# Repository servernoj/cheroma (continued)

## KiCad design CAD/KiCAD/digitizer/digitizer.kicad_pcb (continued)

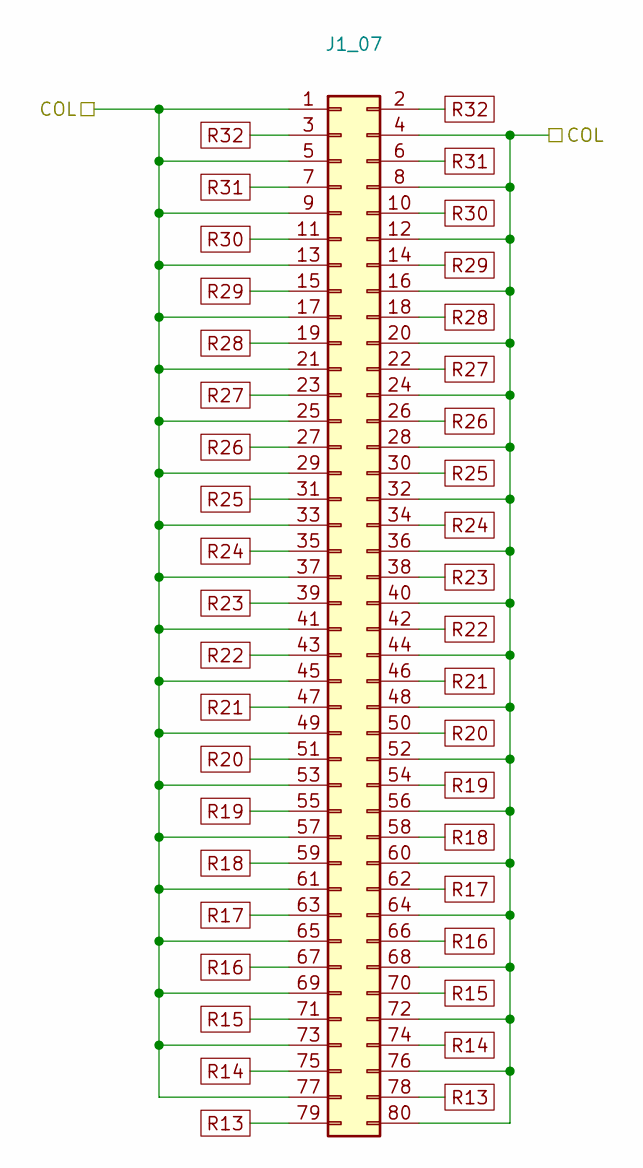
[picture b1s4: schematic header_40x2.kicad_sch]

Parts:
J1_07: Conn_02x40_Odd_Even; PinHeader_2x40_P2.54mm_Vertical

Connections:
C7: J1_07.1, J1_07.4, J1_07.5, J1_07.8, J1_07.9, J1_07.12, J1_07.13, J1_07.16, J1_07.17, J1_07.20, J1_07.21, J1_07.24, J1_07.25, J1_07.28, J1_07.29, J1_07.32, J1_07.33, J1_07.36, J1_07.37, J1_07.40, J1_07.41, J1_07.44, J1_07.45, J1_07.48, J1_07.49, J1_07.52, J1_07.53, J1_07.56, J1_07.57, J1_07.60, J1_07.61, J1_07.64, J1_07.65, J1_07.68, J1_07.69, J1_07.72, J1_07.73, J1_07.76, J1_07.77, J1_07.80; also elsewhere on the board
R13: J1_07.78, J1_07.79; also elsewhere on the board
R14: J1_07.74, J1_07.75; also elsewhere on the board
R15: J1_07.70, J1_07.71; also elsewhere on the board
R16: J1_07.66, J1_07.67; also elsewhere on the board
R17: J1_07.62, J1_07.63; also elsewhere on the board
R18: J1_07.58, J1_07.59; also elsewhere on the board
R19: J1_07.54, J1_07.55; also elsewhere on the board
R20: J1_07.50, J1_07.51; also elsewhere on the board
R21: J1_07.46, J1_07.47; also elsewhere on the board
R22: J1_07.42, J1_07.43; also elsewhere on the board
R23: J1_07.38, J1_07.39; also elsewhere on the board
R24: J1_07.34, J1_07.35; also elsewhere on the board
R25: J1_07.30, J1_07.31; also elsewhere on the board
R26: J1_07.26, J1_07.27; also elsewhere on the board
R27: J1_07.22, J1_07.23; also elsewhere on the board
R28: J1_07.18, J1_07.19; also elsewhere on the board
R29: J1_07.14, J1_07.15; also elsewhere on the board
R30: J1_07.10, J1_07.11; also elsewhere on the board
R31: J1_07.6, J1_07.7; also elsewhere on the board
R32: J1_07.2, J1_07.3; also elsewhere on the board

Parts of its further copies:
J1_01, J1_02, J1_03, J1_04, J1_05, J1_06, J1_08, J1_09, J1_10, J1_11, J1_12, J1_13, J1_14, J1_15, J1_16, J1_17, J1_18, J1_19, J1_20, J1_21, J1_22, J1_23, J1_24, J1_25, J1_26, J1_27, J1_28, J1_29, J1_30, J1_31, J1_32: Conn_02x40_Odd_Even; PinHeader_2x40_P2.54mm_Vertical

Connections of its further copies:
C1: J1_01.1, J1_01.4, J1_01.5, J1_01.8, J1_01.9, J1_01.12, J1_01.13, J1_01.16, J1_01.17, J1_01.20, J1_01.21, J1_01.24, J1_01.25, J1_01.28, J1_01.29, J1_01.32, J1_01.33, J1_01.36, J1_01.37, J1_01.40, J1_01.41, J1_01.44, J1_01.45, J1_01.48, J1_01.49, J1_01.52, J1_01.53, J1_01.56, J1_01.57, J1_01.60, J1_01.61, J1_01.64, J1_01.65, J1_01.68, J1_01.69, J1_01.72, J1_01.73, J1_01.76, J1_01.77, J1_01.80; also elsewhere on the board
C2: J1_02.1, J1_02.4, J1_02.5, J1_02.8, J1_02.9, J1_02.12, J1_02.13, J1_02.16, J1_02.17, J1_02.20, J1_02.21, J1_02.24, J1_02.25, J1_02.28, J1_02.29, J1_02.32, J1_02.33, J1_02.36, J1_02.37, J1_02.40, J1_02.41, J1_02.44, J1_02.45, J1_02.48, J1_02.49, J1_02.52, J1_02.53, J1_02.56, J1_02.57, J1_02.60, J1_02.61, J1_02.64, J1_02.65, J1_02.68, J1_02.69, J1_02.72, J1_02.73, J1_02.76, J1_02.77, J1_02.80; also elsewhere on the board
C3: J1_03.1, J1_03.4, J1_03.5, J1_03.8, J1_03.9, J1_03.12, J1_03.13, J1_03.16, J1_03.17, J1_03.20, J1_03.21, J1_03.24, J1_03.25, J1_03.28, J1_03.29, J1_03.32, J1_03.33, J1_03.36, J1_03.37, J1_03.40, J1_03.41, J1_03.44, J1_03.45, J1_03.48, J1_03.49, J1_03.52, J1_03.53, J1_03.56, J1_03.57, J1_03.60, J1_03.61, J1_03.64, J1_03.65, J1_03.68, J1_03.69, J1_03.72, J1_03.73, J1_03.76, J1_03.77, J1_03.80; also elsewhere on the board
C4: J1_04.1, J1_04.4, J1_04.5, J1_04.8, J1_04.9, J1_04.12, J1_04.13, J1_04.16, J1_04.17, J1_04.20, J1_04.21, J1_04.24, J1_04.25, J1_04.28, J1_04.29, J1_04.32, J1_04.33, J1_04.36, J1_04.37, J1_04.40, J1_04.41, J1_04.44, J1_04.45, J1_04.48, J1_04.49, J1_04.52, J1_04.53, J1_04.56, J1_04.57, J1_04.60, J1_04.61, J1_04.64, J1_04.65, J1_04.68, J1_04.69, J1_04.72, J1_04.73, J1_04.76, J1_04.77, J1_04.80; also elsewhere on the board
C5: J1_05.1, J1_05.4, J1_05.5, J1_05.8, J1_05.9, J1_05.12, J1_05.13, J1_05.16, J1_05.17, J1_05.20, J1_05.21, J1_05.24, J1_05.25, J1_05.28, J1_05.29, J1_05.32, J1_05.33, J1_05.36, J1_05.37, J1_05.40, J1_05.41, J1_05.44, J1_05.45, J1_05.48, J1_05.49, J1_05.52, J1_05.53, J1_05.56, J1_05.57, J1_05.60, J1_05.61, J1_05.64, J1_05.65, J1_05.68, J1_05.69, J1_05.72, J1_05.73, J1_05.76, J1_05.77, J1_05.80; also elsewhere on the board
C6: J1_06.1, J1_06.4, J1_06.5, J1_06.8, J1_06.9, J1_06.12, J1_06.13, J1_06.16, J1_06.17, J1_06.20, J1_06.21, J1_06.24, J1_06.25, J1_06.28, J1_06.29, J1_06.32, J1_06.33, J1_06.36, J1_06.37, J1_06.40, J1_06.41, J1_06.44, J1_06.45, J1_06.48, J1_06.49, J1_06.52, J1_06.53, J1_06.56, J1_06.57, J1_06.60, J1_06.61, J1_06.64, J1_06.65, J1_06.68, J1_06.69, J1_06.72, J1_06.73, J1_06.76, J1_06.77, J1_06.80; also elsewhere on the board
C8: J1_08.1, J1_08.4, J1_08.5, J1_08.8, J1_08.9, J1_08.12, J1_08.13, J1_08.16, J1_08.17, J1_08.20, J1_08.21, J1_08.24, J1_08.25, J1_08.28, J1_08.29, J1_08.32, J1_08.33, J1_08.36, J1_08.37, J1_08.40, J1_08.41, J1_08.44, J1_08.45, J1_08.48, J1_08.49, J1_08.52, J1_08.53, J1_08.56, J1_08.57, J1_08.60, J1_08.61, J1_08.64, J1_08.65, J1_08.68, J1_08.69, J1_08.72, J1_08.73, J1_08.76, J1_08.77, J1_08.80; also elsewhere on the board
C9: J1_09.1, J1_09.4, J1_09.5, J1_09.8, J1_09.9, J1_09.12, J1_09.13, J1_09.16, J1_09.17, J1_09.20, J1_09.21, J1_09.24, J1_09.25, J1_09.28, J1_09.29, J1_09.32, J1_09.33, J1_09.36, J1_09.37, J1_09.40, J1_09.41, J1_09.44, J1_09.45, J1_09.48, J1_09.49, J1_09.52, J1_09.53, J1_09.56, J1_09.57, J1_09.60, J1_09.61, J1_09.64, J1_09.65, J1_09.68, J1_09.69, J1_09.72, J1_09.73, J1_09.76, J1_09.77, J1_09.80; also elsewhere on the board
C10: J1_10.1, J1_10.4, J1_10.5, J1_10.8, J1_10.9, J1_10.12, J1_10.13, J1_10.16, J1_10.17, J1_10.20, J1_10.21, J1_10.24, J1_10.25, J1_10.28, J1_10.29, J1_10.32, J1_10.33, J1_10.36, J1_10.37, J1_10.40, J1_10.41, J1_10.44, J1_10.45, J1_10.48, J1_10.49, J1_10.52, J1_10.53, J1_10.56, J1_10.57, J1_10.60, J1_10.61, J1_10.64, J1_10.65, J1_10.68, J1_10.69, J1_10.72, J1_10.73, J1_10.76, J1_10.77, J1_10.80; also elsewhere on the board
C11: J1_11.1, J1_11.4, J1_11.5, J1_11.8, J1_11.9, J1_11.12, J1_11.13, J1_11.16, J1_11.17, J1_11.20, J1_11.21, J1_11.24, J1_11.25, J1_11.28, J1_11.29, J1_11.32, J1_11.33, J1_11.36, J1_11.37, J1_11.40, J1_11.41, J1_11.44, J1_11.45, J1_11.48, J1_11.49, J1_11.52, J1_11.53, J1_11.56, J1_11.57, J1_11.60, J1_11.61, J1_11.64, J1_11.65, J1_11.68, J1_11.69, J1_11.72, J1_11.73, J1_11.76, J1_11.77, J1_11.80; also elsewhere on the board
C12: J1_12.1, J1_12.4, J1_12.5, J1_12.8, J1_12.9, J1_12.12, J1_12.13, J1_12.16, J1_12.17, J1_12.20, J1_12.21, J1_12.24, J1_12.25, J1_12.28, J1_12.29, J1_12.32, J1_12.33, J1_12.36, J1_12.37, J1_12.40, J1_12.41, J1_12.44, J1_12.45, J1_12.48, J1_12.49, J1_12.52, J1_12.53, J1_12.56, J1_12.57, J1_12.60, J1_12.61, J1_12.64, J1_12.65, J1_12.68, J1_12.69, J1_12.72, J1_12.73, J1_12.76, J1_12.77, J1_12.80; also elsewhere on the board
C13: J1_13.1, J1_13.4, J1_13.5, J1_13.8, J1_13.9, J1_13.12, J1_13.13, J1_13.16, J1_13.17, J1_13.20, J1_13.21, J1_13.24, J1_13.25, J1_13.28, J1_13.29, J1_13.32, J1_13.33, J1_13.36, J1_13.37, J1_13.40, J1_13.41, J1_13.44, J1_13.45, J1_13.48, J1_13.49, J1_13.52, J1_13.53, J1_13.56, J1_13.57, J1_13.60, J1_13.61, J1_13.64, J1_13.65, J1_13.68, J1_13.69, J1_13.72, J1_13.73, J1_13.76, J1_13.77, J1_13.80; also elsewhere on the board
C14: J1_14.1, J1_14.4, J1_14.5, J1_14.8, J1_14.9, J1_14.12, J1_14.13, J1_14.16, J1_14.17, J1_14.20, J1_14.21, J1_14.24, J1_14.25, J1_14.28, J1_14.29, J1_14.32, J1_14.33, J1_14.36, J1_14.37, J1_14.40, J1_14.41, J1_14.44, J1_14.45, J1_14.48, J1_14.49, J1_14.52, J1_14.53, J1_14.56, J1_14.57, J1_14.60, J1_14.61, J1_14.64, J1_14.65, J1_14.68, J1_14.69, J1_14.72, J1_14.73, J1_14.76, J1_14.77, J1_14.80; also elsewhere on the board
C15: J1_15.1, J1_15.4, J1_15.5, J1_15.8, J1_15.9, J1_15.12, J1_15.13, J1_15.16, J1_15.17, J1_15.20, J1_15.21, J1_15.24, J1_15.25, J1_15.28, J1_15.29, J1_15.32, J1_15.33, J1_15.36, J1_15.37, J1_15.40, J1_15.41, J1_15.44, J1_15.45, J1_15.48, J1_15.49, J1_15.52, J1_15.53, J1_15.56, J1_15.57, J1_15.60, J1_15.61, J1_15.64, J1_15.65, J1_15.68, J1_15.69, J1_15.72, J1_15.73, J1_15.76, J1_15.77, J1_15.80; also elsewhere on the board
C16: J1_16.1, J1_16.4, J1_16.5, J1_16.8, J1_16.9, J1_16.12, J1_16.13, J1_16.16, J1_16.17, J1_16.20, J1_16.21, J1_16.24, J1_16.25, J1_16.28, J1_16.29, J1_16.32, J1_16.33, J1_16.36, J1_16.37, J1_16.40, J1_16.41, J1_16.44, J1_16.45, J1_16.48, J1_16.49, J1_16.52, J1_16.53, J1_16.56, J1_16.57, J1_16.60, J1_16.61, J1_16.64, J1_16.65, J1_16.68, J1_16.69, J1_16.72, J1_16.73, J1_16.76, J1_16.77, J1_16.80; also elsewhere on the board
C17: J1_17.1, J1_17.4, J1_17.5, J1_17.8, J1_17.9, J1_17.12, J1_17.13, J1_17.16, J1_17.17, J1_17.20, J1_17.21, J1_17.24, J1_17.25, J1_17.28, J1_17.29, J1_17.32, J1_17.33, J1_17.36, J1_17.37, J1_17.40, J1_17.41, J1_17.44, J1_17.45, J1_17.48, J1_17.49, J1_17.52, J1_17.53, J1_17.56, J1_17.57, J1_17.60, J1_17.61, J1_17.64, J1_17.65, J1_17.68, J1_17.69, J1_17.72, J1_17.73, J1_17.76, J1_17.77, J1_17.80; also elsewhere on the board
C18: J1_18.1, J1_18.4, J1_18.5, J1_18.8, J1_18.9, J1_18.12, J1_18.13, J1_18.16, J1_18.17, J1_18.20, J1_18.21, J1_18.24, J1_18.25, J1_18.28, J1_18.29, J1_18.32, J1_18.33, J1_18.36, J1_18.37, J1_18.40, J1_18.41, J1_18.44, J1_18.45, J1_18.48, J1_18.49, J1_18.52, J1_18.53, J1_18.56, J1_18.57, J1_18.60, J1_18.61, J1_18.64, J1_18.65, J1_18.68, J1_18.69, J1_18.72, J1_18.73, J1_18.76, J1_18.77, J1_18.80; also elsewhere on the board
C19: J1_19.1, J1_19.4, J1_19.5, J1_19.8, J1_19.9, J1_19.12, J1_19.13, J1_19.16, J1_19.17, J1_19.20, J1_19.21, J1_19.24, J1_19.25, J1_19.28, J1_19.29, J1_19.32, J1_19.33, J1_19.36, J1_19.37, J1_19.40, J1_19.41, J1_19.44, J1_19.45, J1_19.48, J1_19.49, J1_19.52, J1_19.53, J1_19.56, J1_19.57, J1_19.60, J1_19.61, J1_19.64, J1_19.65, J1_19.68, J1_19.69, J1_19.72, J1_19.73, J1_19.76, J1_19.77, J1_19.80; also elsewhere on the board
C20: J1_20.1, J1_20.4, J1_20.5, J1_20.8, J1_20.9, J1_20.12, J1_20.13, J1_20.16, J1_20.17, J1_20.20, J1_20.21, J1_20.24, J1_20.25, J1_20.28, J1_20.29, J1_20.32, J1_20.33, J1_20.36, J1_20.37, J1_20.40, J1_20.41, J1_20.44, J1_20.45, J1_20.48, J1_20.49, J1_20.52, J1_20.53, J1_20.56, J1_20.57, J1_20.60, J1_20.61, J1_20.64, J1_20.65, J1_20.68, J1_20.69, J1_20.72, J1_20.73, J1_20.76, J1_20.77, J1_20.80; also elsewhere on the board
C21: J1_21.1, J1_21.4, J1_21.5, J1_21.8, J1_21.9, J1_21.12, J1_21.13, J1_21.16, J1_21.17, J1_21.20, J1_21.21, J1_21.24, J1_21.25, J1_21.28, J1_21.29, J1_21.32, J1_21.33, J1_21.36, J1_21.37, J1_21.40, J1_21.41, J1_21.44, J1_21.45, J1_21.48, J1_21.49, J1_21.52, J1_21.53, J1_21.56, J1_21.57, J1_21.60, J1_21.61, J1_21.64, J1_21.65, J1_21.68, J1_21.69, J1_21.72, J1_21.73, J1_21.76, J1_21.77, J1_21.80; also elsewhere on the board
C22: J1_22.1, J1_22.4, J1_22.5, J1_22.8, J1_22.9, J1_22.12, J1_22.13, J1_22.16, J1_22.17, J1_22.20, J1_22.21, J1_22.24, J1_22.25, J1_22.28, J1_22.29, J1_22.32, J1_22.33, J1_22.36, J1_22.37, J1_22.40, J1_22.41, J1_22.44, J1_22.45, J1_22.48, J1_22.49, J1_22.52, J1_22.53, J1_22.56, J1_22.57, J1_22.60, J1_22.61, J1_22.64, J1_22.65, J1_22.68, J1_22.69, J1_22.72, J1_22.73, J1_22.76, J1_22.77, J1_22.80; also elsewhere on the board
C23: J1_23.1, J1_23.4, J1_23.5, J1_23.8, J1_23.9, J1_23.12, J1_23.13, J1_23.16, J1_23.17, J1_23.20, J1_23.21, J1_23.24, J1_23.25, J1_23.28, J1_23.29, J1_23.32, J1_23.33, J1_23.36, J1_23.37, J1_23.40, J1_23.41, J1_23.44, J1_23.45, J1_23.48, J1_23.49, J1_23.52, J1_23.53, J1_23.56, J1_23.57, J1_23.60, J1_23.61, J1_23.64, J1_23.65, J1_23.68, J1_23.69, J1_23.72, J1_23.73, J1_23.76, J1_23.77, J1_23.80; also elsewhere on the board
C24: J1_24.1, J1_24.4, J1_24.5, J1_24.8, J1_24.9, J1_24.12, J1_24.13, J1_24.16, J1_24.17, J1_24.20, J1_24.21, J1_24.24, J1_24.25, J1_24.28, J1_24.29, J1_24.32, J1_24.33, J1_24.36, J1_24.37, J1_24.40, J1_24.41, J1_24.44, J1_24.45, J1_24.48, J1_24.49, J1_24.52, J1_24.53, J1_24.56, J1_24.57, J1_24.60, J1_24.61, J1_24.64, J1_24.65, J1_24.68, J1_24.69, J1_24.72, J1_24.73, J1_24.76, J1_24.77, J1_24.80; also elsewhere on the board
C25: J1_25.1, J1_25.4, J1_25.5, J1_25.8, J1_25.9, J1_25.12, J1_25.13, J1_25.16, J1_25.17, J1_25.20, J1_25.21, J1_25.24, J1_25.25, J1_25.28, J1_25.29, J1_25.32, J1_25.33, J1_25.36, J1_25.37, J1_25.40, J1_25.41, J1_25.44, J1_25.45, J1_25.48, J1_25.49, J1_25.52, J1_25.53, J1_25.56, J1_25.57, J1_25.60, J1_25.61, J1_25.64, J1_25.65, J1_25.68, J1_25.69, J1_25.72, J1_25.73, J1_25.76, J1_25.77, J1_25.80; also elsewhere on the board
C26: J1_26.1, J1_26.4, J1_26.5, J1_26.8, J1_26.9, J1_26.12, J1_26.13, J1_26.16, J1_26.17, J1_26.20, J1_26.21, J1_26.24, J1_26.25, J1_26.28, J1_26.29, J1_26.32, J1_26.33, J1_26.36, J1_26.37, J1_26.40, J1_26.41, J1_26.44, J1_26.45, J1_26.48, J1_26.49, J1_26.52, J1_26.53, J1_26.56, J1_26.57, J1_26.60, J1_26.61, J1_26.64, J1_26.65, J1_26.68, J1_26.69, J1_26.72, J1_26.73, J1_26.76, J1_26.77, J1_26.80; also elsewhere on the board
C27: J1_27.1, J1_27.4, J1_27.5, J1_27.8, J1_27.9, J1_27.12, J1_27.13, J1_27.16, J1_27.17, J1_27.20, J1_27.21, J1_27.24, J1_27.25, J1_27.28, J1_27.29, J1_27.32, J1_27.33, J1_27.36, J1_27.37, J1_27.40, J1_27.41, J1_27.44, J1_27.45, J1_27.48, J1_27.49, J1_27.52, J1_27.53, J1_27.56, J1_27.57, J1_27.60, J1_27.61, J1_27.64, J1_27.65, J1_27.68, J1_27.69, J1_27.72, J1_27.73, J1_27.76, J1_27.77, J1_27.80; also elsewhere on the board
C28: J1_28.1, J1_28.4, J1_28.5, J1_28.8, J1_28.9, J1_28.12, J1_28.13, J1_28.16, J1_28.17, J1_28.20, J1_28.21, J1_28.24, J1_28.25, J1_28.28, J1_28.29, J1_28.32, J1_28.33, J1_28.36, J1_28.37, J1_28.40, J1_28.41, J1_28.44, J1_28.45, J1_28.48, J1_28.49, J1_28.52, J1_28.53, J1_28.56, J1_28.57, J1_28.60, J1_28.61, J1_28.64, J1_28.65, J1_28.68, J1_28.69, J1_28.72, J1_28.73, J1_28.76, J1_28.77, J1_28.80; also elsewhere on the board
C29: J1_29.1, J1_29.4, J1_29.5, J1_29.8, J1_29.9, J1_29.12, J1_29.13, J1_29.16, J1_29.17, J1_29.20, J1_29.21, J1_29.24, J1_29.25, J1_29.28, J1_29.29, J1_29.32, J1_29.33, J1_29.36, J1_29.37, J1_29.40, J1_29.41, J1_29.44, J1_29.45, J1_29.48, J1_29.49, J1_29.52, J1_29.53, J1_29.56, J1_29.57, J1_29.60, J1_29.61, J1_29.64, J1_29.65, J1_29.68, J1_29.69, J1_29.72, J1_29.73, J1_29.76, J1_29.77, J1_29.80; also elsewhere on the board
C30: J1_30.1, J1_30.4, J1_30.5, J1_30.8, J1_30.9, J1_30.12, J1_30.13, J1_30.16, J1_30.17, J1_30.20, J1_30.21, J1_30.24, J1_30.25, J1_30.28, J1_30.29, J1_30.32, J1_30.33, J1_30.36, J1_30.37, J1_30.40, J1_30.41, J1_30.44, J1_30.45, J1_30.48, J1_30.49, J1_30.52, J1_30.53, J1_30.56, J1_30.57, J1_30.60, J1_30.61, J1_30.64, J1_30.65, J1_30.68, J1_30.69, J1_30.72, J1_30.73, J1_30.76, J1_30.77, J1_30.80; also elsewhere on the board
C31: J1_31.1, J1_31.4, J1_31.5, J1_31.8, J1_31.9, J1_31.12, J1_31.13, J1_31.16, J1_31.17, J1_31.20, J1_31.21, J1_31.24, J1_31.25, J1_31.28, J1_31.29, J1_31.32, J1_31.33, J1_31.36, J1_31.37, J1_31.40, J1_31.41, J1_31.44, J1_31.45, J1_31.48, J1_31.49, J1_31.52, J1_31.53, J1_31.56, J1_31.57, J1_31.60, J1_31.61, J1_31.64, J1_31.65, J1_31.68, J1_31.69, J1_31.72, J1_31.73, J1_31.76, J1_31.77, J1_31.80; also elsewhere on the board
C32: J1_32.1, J1_32.4, J1_32.5, J1_32.8, J1_32.9, J1_32.12, J1_32.13, J1_32.16, J1_32.17, J1_32.20, J1_32.21, J1_32.24, J1_32.25, J1_32.28, J1_32.29, J1_32.32, J1_32.33, J1_32.36, J1_32.37, J1_32.40, J1_32.41, J1_32.44, J1_32.45, J1_32.48, J1_32.49, J1_32.52, J1_32.53, J1_32.56, J1_32.57, J1_32.60, J1_32.61, J1_32.64, J1_32.65, J1_32.68, J1_32.69, J1_32.72, J1_32.73, J1_32.76, J1_32.77, J1_32.80; also elsewhere on the board
R13: J1_01.78, J1_01.79, J1_02.78, J1_02.79, J1_03.78, J1_03.79, J1_04.78, J1_04.79, J1_05.78, J1_05.79, J1_06.78, J1_06.79, J1_08.78, J1_08.79, J1_09.78, J1_09.79, J1_10.78, J1_10.79, J1_11.78, J1_11.79, J1_12.78, J1_12.79, J1_13.78, J1_13.79, J1_14.78, J1_14.79, J1_15.78, J1_15.79, J1_16.78, J1_16.79, J1_17.78, J1_17.79, J1_18.78, J1_18.79, J1_19.78, J1_19.79, J1_20.78, J1_20.79, J1_21.78, J1_21.79, J1_22.78, J1_22.79, J1_23.78, J1_23.79, J1_24.78, J1_24.79, J1_25.78, J1_25.79, J1_26.78, J1_26.79, J1_27.78, J1_27.79, J1_28.78, J1_28.79, J1_29.78, J1_29.79, J1_30.78, J1_30.79, J1_31.78, J1_31.79, J1_32.78, J1_32.79; also elsewhere on the board
R14: J1_01.74, J1_01.75, J1_02.74, J1_02.75, J1_03.74, J1_03.75, J1_04.74, J1_04.75, J1_05.74, J1_05.75, J1_06.74, J1_06.75, J1_08.74, J1_08.75, J1_09.74, J1_09.75, J1_10.74, J1_10.75, J1_11.74, J1_11.75, J1_12.74, J1_12.75, J1_13.74, J1_13.75, J1_14.74, J1_14.75, J1_15.74, J1_15.75, J1_16.74, J1_16.75, J1_17.74, J1_17.75, J1_18.74, J1_18.75, J1_19.74, J1_19.75, J1_20.74, J1_20.75, J1_21.74, J1_21.75, J1_22.74, J1_22.75, J1_23.74, J1_23.75, J1_24.74, J1_24.75, J1_25.74, J1_25.75, J1_26.74, J1_26.75, J1_27.74, J1_27.75, J1_28.74, J1_28.75, J1_29.74, J1_29.75, J1_30.74, J1_30.75, J1_31.74, J1_31.75, J1_32.74, J1_32.75; also elsewhere on the board
R15: J1_01.70, J1_01.71, J1_02.70, J1_02.71, J1_03.70, J1_03.71, J1_04.70, J1_04.71, J1_05.70, J1_05.71, J1_06.70, J1_06.71, J1_08.70, J1_08.71, J1_09.70, J1_09.71, J1_10.70, J1_10.71, J1_11.70, J1_11.71, J1_12.70, J1_12.71, J1_13.70, J1_13.71, J1_14.70, J1_14.71, J1_15.70, J1_15.71, J1_16.70, J1_16.71, J1_17.70, J1_17.71, J1_18.70, J1_18.71, J1_19.70, J1_19.71, J1_20.70, J1_20.71, J1_21.70, J1_21.71, J1_22.70, J1_22.71, J1_23.70, J1_23.71, J1_24.70, J1_24.71, J1_25.70, J1_25.71, J1_26.70, J1_26.71, J1_27.70, J1_27.71, J1_28.70, J1_28.71, J1_29.70, J1_29.71, J1_30.70, J1_30.71, J1_31.70, J1_31.71, J1_32.70, J1_32.71; also elsewhere on the board
R16: J1_01.66, J1_01.67, J1_02.66, J1_02.67, J1_03.66, J1_03.67, J1_04.66, J1_04.67, J1_05.66, J1_05.67, J1_06.66, J1_06.67, J1_08.66, J1_08.67, J1_09.66, J1_09.67, J1_10.66, J1_10.67, J1_11.66, J1_11.67, J1_12.66, J1_12.67, J1_13.66, J1_13.67, J1_14.66, J1_14.67, J1_15.66, J1_15.67, J1_16.66, J1_16.67, J1_17.66, J1_17.67, J1_18.66, J1_18.67, J1_19.66, J1_19.67, J1_20.66, J1_20.67, J1_21.66, J1_21.67, J1_22.66, J1_22.67, J1_23.66, J1_23.67, J1_24.66, J1_24.67, J1_25.66, J1_25.67, J1_26.66, J1_26.67, J1_27.66, J1_27.67, J1_28.66, J1_28.67, J1_29.66, J1_29.67, J1_30.66, J1_30.67, J1_31.66, J1_31.67, J1_32.66, J1_32.67; also elsewhere on the board
R17: J1_01.62, J1_01.63, J1_02.62, J1_02.63, J1_03.62, J1_03.63, J1_04.62, J1_04.63, J1_05.62, J1_05.63, J1_06.62, J1_06.63, J1_08.62, J1_08.63, J1_09.62, J1_09.63, J1_10.62, J1_10.63, J1_11.62, J1_11.63, J1_12.62, J1_12.63, J1_13.62, J1_13.63, J1_14.62, J1_14.63, J1_15.62, J1_15.63, J1_16.62, J1_16.63, J1_17.62, J1_17.63, J1_18.62, J1_18.63, J1_19.62, J1_19.63, J1_20.62, J1_20.63, J1_21.62, J1_21.63, J1_22.62, J1_22.63, J1_23.62, J1_23.63, J1_24.62, J1_24.63, J1_25.62, J1_25.63, J1_26.62, J1_26.63, J1_27.62, J1_27.63, J1_28.62, J1_28.63, J1_29.62, J1_29.63, J1_30.62, J1_30.63, J1_31.62, J1_31.63, J1_32.62, J1_32.63; also elsewhere on the board
R18: J1_01.58, J1_01.59, J1_02.58, J1_02.59, J1_03.58, J1_03.59, J1_04.58, J1_04.59, J1_05.58, J1_05.59, J1_06.58, J1_06.59, J1_08.58, J1_08.59, J1_09.58, J1_09.59, J1_10.58, J1_10.59, J1_11.58, J1_11.59, J1_12.58, J1_12.59, J1_13.58, J1_13.59, J1_14.58, J1_14.59, J1_15.58, J1_15.59, J1_16.58, J1_16.59, J1_17.58, J1_17.59, J1_18.58, J1_18.59, J1_19.58, J1_19.59, J1_20.58, J1_20.59, J1_21.58, J1_21.59, J1_22.58, J1_22.59, J1_23.58, J1_23.59, J1_24.58, J1_24.59, J1_25.58, J1_25.59, J1_26.58, J1_26.59, J1_27.58, J1_27.59, J1_28.58, J1_28.59, J1_29.58, J1_29.59, J1_30.58, J1_30.59, J1_31.58, J1_31.59, J1_32.58, J1_32.59; also elsewhere on the board
R19: J1_01.54, J1_01.55, J1_02.54, J1_02.55, J1_03.54, J1_03.55, J1_04.54, J1_04.55, J1_05.54, J1_05.55, J1_06.54, J1_06.55, J1_08.54, J1_08.55, J1_09.54, J1_09.55, J1_10.54, J1_10.55, J1_11.54, J1_11.55, J1_12.54, J1_12.55, J1_13.54, J1_13.55, J1_14.54, J1_14.55, J1_15.54, J1_15.55, J1_16.54, J1_16.55, J1_17.54, J1_17.55, J1_18.54, J1_18.55, J1_19.54, J1_19.55, J1_20.54, J1_20.55, J1_21.54, J1_21.55, J1_22.54, J1_22.55, J1_23.54, J1_23.55, J1_24.54, J1_24.55, J1_25.54, J1_25.55, J1_26.54, J1_26.55, J1_27.54, J1_27.55, J1_28.54, J1_28.55, J1_29.54, J1_29.55, J1_30.54, J1_30.55, J1_31.54, J1_31.55, J1_32.54, J1_32.55; also elsewhere on the board
R20: J1_01.50, J1_01.51, J1_02.50, J1_02.51, J1_03.50, J1_03.51, J1_04.50, J1_04.51, J1_05.50, J1_05.51, J1_06.50, J1_06.51, J1_08.50, J1_08.51, J1_09.50, J1_09.51, J1_10.50, J1_10.51, J1_11.50, J1_11.51, J1_12.50, J1_12.51, J1_13.50, J1_13.51, J1_14.50, J1_14.51, J1_15.50, J1_15.51, J1_16.50, J1_16.51, J1_17.50, J1_17.51, J1_18.50, J1_18.51, J1_19.50, J1_19.51, J1_20.50, J1_20.51, J1_21.50, J1_21.51, J1_22.50, J1_22.51, J1_23.50, J1_23.51, J1_24.50, J1_24.51, J1_25.50, J1_25.51, J1_26.50, J1_26.51, J1_27.50, J1_27.51, J1_28.50, J1_28.51, J1_29.50, J1_29.51, J1_30.50, J1_30.51, J1_31.50, J1_31.51, J1_32.50, J1_32.51; also elsewhere on the board
R21: J1_01.46, J1_01.47, J1_02.46, J1_02.47, J1_03.46, J1_03.47, J1_04.46, J1_04.47, J1_05.46, J1_05.47, J1_06.46, J1_06.47, J1_08.46, J1_08.47, J1_09.46, J1_09.47, J1_10.46, J1_10.47, J1_11.46, J1_11.47, J1_12.46, J1_12.47, J1_13.46, J1_13.47, J1_14.46, J1_14.47, J1_15.46, J1_15.47, J1_16.46, J1_16.47, J1_17.46, J1_17.47, J1_18.46, J1_18.47, J1_19.46, J1_19.47, J1_20.46, J1_20.47, J1_21.46, J1_21.47, J1_22.46, J1_22.47, J1_23.46, J1_23.47, J1_24.46, J1_24.47, J1_25.46, J1_25.47, J1_26.46, J1_26.47, J1_27.46, J1_27.47, J1_28.46, J1_28.47, J1_29.46, J1_29.47, J1_30.46, J1_30.47, J1_31.46, J1_31.47, J1_32.46, J1_32.47; also elsewhere on the board
R22: J1_01.42, J1_01.43, J1_02.42, J1_02.43, J1_03.42, J1_03.43, J1_04.42, J1_04.43, J1_05.42, J1_05.43, J1_06.42, J1_06.43, J1_08.42, J1_08.43, J1_09.42, J1_09.43, J1_10.42, J1_10.43, J1_11.42, J1_11.43, J1_12.42, J1_12.43, J1_13.42, J1_13.43, J1_14.42, J1_14.43, J1_15.42, J1_15.43, J1_16.42, J1_16.43, J1_17.42, J1_17.43, J1_18.42, J1_18.43, J1_19.42, J1_19.43, J1_20.42, J1_20.43, J1_21.42, J1_21.43, J1_22.42, J1_22.43, J1_23.42, J1_23.43, J1_24.42, J1_24.43, J1_25.42, J1_25.43, J1_26.42, J1_26.43, J1_27.42, J1_27.43, J1_28.42, J1_28.43, J1_29.42, J1_29.43, J1_30.42, J1_30.43, J1_31.42, J1_31.43, J1_32.42, J1_32.43; also elsewhere on the board
R23: J1_01.38, J1_01.39, J1_02.38, J1_02.39, J1_03.38, J1_03.39, J1_04.38, J1_04.39, J1_05.38, J1_05.39, J1_06.38, J1_06.39, J1_08.38, J1_08.39, J1_09.38, J1_09.39, J1_10.38, J1_10.39, J1_11.38, J1_11.39, J1_12.38, J1_12.39, J1_13.38, J1_13.39, J1_14.38, J1_14.39, J1_15.38, J1_15.39, J1_16.38, J1_16.39, J1_17.38, J1_17.39, J1_18.38, J1_18.39, J1_19.38, J1_19.39, J1_20.38, J1_20.39, J1_21.38, J1_21.39, J1_22.38, J1_22.39, J1_23.38, J1_23.39, J1_24.38, J1_24.39, J1_25.38, J1_25.39, J1_26.38, J1_26.39, J1_27.38, J1_27.39, J1_28.38, J1_28.39, J1_29.38, J1_29.39, J1_30.38, J1_30.39, J1_31.38, J1_31.39, J1_32.38, J1_32.39; also elsewhere on the board
R24: J1_01.34, J1_01.35, J1_02.34, J1_02.35, J1_03.34, J1_03.35, J1_04.34, J1_04.35, J1_05.34, J1_05.35, J1_06.34, J1_06.35, J1_08.34, J1_08.35, J1_09.34, J1_09.35, J1_10.34, J1_10.35, J1_11.34, J1_11.35, J1_12.34, J1_12.35, J1_13.34, J1_13.35, J1_14.34, J1_14.35, J1_15.34, J1_15.35, J1_16.34, J1_16.35, J1_17.34, J1_17.35, J1_18.34, J1_18.35, J1_19.34, J1_19.35, J1_20.34, J1_20.35, J1_21.34, J1_21.35, J1_22.34, J1_22.35, J1_23.34, J1_23.35, J1_24.34, J1_24.35, J1_25.34, J1_25.35, J1_26.34, J1_26.35, J1_27.34, J1_27.35, J1_28.34, J1_28.35, J1_29.34, J1_29.35, J1_30.34, J1_30.35, J1_31.34, J1_31.35, J1_32.34, J1_32.35; also elsewhere on the board
R25: J1_01.30, J1_01.31, J1_02.30, J1_02.31, J1_03.30, J1_03.31, J1_04.30, J1_04.31, J1_05.30, J1_05.31, J1_06.30, J1_06.31, J1_08.30, J1_08.31, J1_09.30, J1_09.31, J1_10.30, J1_10.31, J1_11.30, J1_11.31, J1_12.30, J1_12.31, J1_13.30, J1_13.31, J1_14.30, J1_14.31, J1_15.30, J1_15.31, J1_16.30, J1_16.31, J1_17.30, J1_17.31, J1_18.30, J1_18.31, J1_19.30, J1_19.31, J1_20.30, J1_20.31, J1_21.30, J1_21.31, J1_22.30, J1_22.31, J1_23.30, J1_23.31, J1_24.30, J1_24.31, J1_25.30, J1_25.31, J1_26.30, J1_26.31, J1_27.30, J1_27.31, J1_28.30, J1_28.31, J1_29.30, J1_29.31, J1_30.30, J1_30.31, J1_31.30, J1_31.31, J1_32.30, J1_32.31; also elsewhere on the board
R26: J1_01.26, J1_01.27, J1_02.26, J1_02.27, J1_03.26, J1_03.27, J1_04.26, J1_04.27, J1_05.26, J1_05.27, J1_06.26, J1_06.27, J1_08.26, J1_08.27, J1_09.26, J1_09.27, J1_10.26, J1_10.27, J1_11.26, J1_11.27, J1_12.26, J1_12.27, J1_13.26, J1_13.27, J1_14.26, J1_14.27, J1_15.26, J1_15.27, J1_16.26, J1_16.27, J1_17.26, J1_17.27, J1_18.26, J1_18.27, J1_19.26, J1_19.27, J1_20.26, J1_20.27, J1_21.26, J1_21.27, J1_22.26, J1_22.27, J1_23.26, J1_23.27, J1_24.26, J1_24.27, J1_25.26, J1_25.27, J1_26.26, J1_26.27, J1_27.26, J1_27.27, J1_28.26, J1_28.27, J1_29.26, J1_29.27, J1_30.26, J1_30.27, J1_31.26, J1_31.27, J1_32.26, J1_32.27; also elsewhere on the board
R27: J1_01.22, J1_01.23, J1_02.22, J1_02.23, J1_03.22, J1_03.23, J1_04.22, J1_04.23, J1_05.22, J1_05.23, J1_06.22, J1_06.23, J1_08.22, J1_08.23, J1_09.22, J1_09.23, J1_10.22, J1_10.23, J1_11.22, J1_11.23, J1_12.22, J1_12.23, J1_13.22, J1_13.23, J1_14.22, J1_14.23, J1_15.22, J1_15.23, J1_16.22, J1_16.23, J1_17.22, J1_17.23, J1_18.22, J1_18.23, J1_19.22, J1_19.23, J1_20.22, J1_20.23, J1_21.22, J1_21.23, J1_22.22, J1_22.23, J1_23.22, J1_23.23, J1_24.22, J1_24.23, J1_25.22, J1_25.23, J1_26.22, J1_26.23, J1_27.22, J1_27.23, J1_28.22, J1_28.23, J1_29.22, J1_29.23, J1_30.22, J1_30.23, J1_31.22, J1_31.23, J1_32.22, J1_32.23; also elsewhere on the board
R28: J1_01.18, J1_01.19, J1_02.18, J1_02.19, J1_03.18, J1_03.19, J1_04.18, J1_04.19, J1_05.18, J1_05.19, J1_06.18, J1_06.19, J1_08.18, J1_08.19, J1_09.18, J1_09.19, J1_10.18, J1_10.19, J1_11.18, J1_11.19, J1_12.18, J1_12.19, J1_13.18, J1_13.19, J1_14.18, J1_14.19, J1_15.18, J1_15.19, J1_16.18, J1_16.19, J1_17.18, J1_17.19, J1_18.18, J1_18.19, J1_19.18, J1_19.19, J1_20.18, J1_20.19, J1_21.18, J1_21.19, J1_22.18, J1_22.19, J1_23.18, J1_23.19, J1_24.18, J1_24.19, J1_25.18, J1_25.19, J1_26.18, J1_26.19, J1_27.18, J1_27.19, J1_28.18, J1_28.19, J1_29.18, J1_29.19, J1_30.18, J1_30.19, J1_31.18, J1_31.19, J1_32.18, J1_32.19; also elsewhere on the board
R29: J1_01.14, J1_01.15, J1_02.14, J1_02.15, J1_03.14, J1_03.15, J1_04.14, J1_04.15, J1_05.14, J1_05.15, J1_06.14, J1_06.15, J1_08.14, J1_08.15, J1_09.14, J1_09.15, J1_10.14, J1_10.15, J1_11.14, J1_11.15, J1_12.14, J1_12.15, J1_13.14, J1_13.15, J1_14.14, J1_14.15, J1_15.14, J1_15.15, J1_16.14, J1_16.15, J1_17.14, J1_17.15, J1_18.14, J1_18.15, J1_19.14, J1_19.15, J1_20.14, J1_20.15, J1_21.14, J1_21.15, J1_22.14, J1_22.15, J1_23.14, J1_23.15, J1_24.14, J1_24.15, J1_25.14, J1_25.15, J1_26.14, J1_26.15, J1_27.14, J1_27.15, J1_28.14, J1_28.15, J1_29.14, J1_29.15, J1_30.14, J1_30.15, J1_31.14, J1_31.15, J1_32.14, J1_32.15; also elsewhere on the board
R30: J1_01.10, J1_01.11, J1_02.10, J1_02.11, J1_03.10, J1_03.11, J1_04.10, J1_04.11, J1_05.10, J1_05.11, J1_06.10, J1_06.11, J1_08.10, J1_08.11, J1_09.10, J1_09.11, J1_10.10, J1_10.11, J1_11.10, J1_11.11, J1_12.10, J1_12.11, J1_13.10, J1_13.11, J1_14.10, J1_14.11, J1_15.10, J1_15.11, J1_16.10, J1_16.11, J1_17.10, J1_17.11, J1_18.10, J1_18.11, J1_19.10, J1_19.11, J1_20.10, J1_20.11, J1_21.10, J1_21.11, J1_22.10, J1_22.11, J1_23.10, J1_23.11, J1_24.10, J1_24.11, J1_25.10, J1_25.11, J1_26.10, J1_26.11, J1_27.10, J1_27.11, J1_28.10, J1_28.11, J1_29.10, J1_29.11, J1_30.10, J1_30.11, J1_31.10, J1_31.11, J1_32.10, J1_32.11; also elsewhere on the board
R31: J1_01.6, J1_01.7, J1_02.6, J1_02.7, J1_03.6, J1_03.7, J1_04.6, J1_04.7, J1_05.6, J1_05.7, J1_06.6, J1_06.7, J1_08.6, J1_08.7, J1_09.6, J1_09.7, J1_10.6, J1_10.7, J1_11.6, J1_11.7, J1_12.6, J1_12.7, J1_13.6, J1_13.7, J1_14.6, J1_14.7, J1_15.6, J1_15.7, J1_16.6, J1_16.7, J1_17.6, J1_17.7, J1_18.6, J1_18.7, J1_19.6, J1_19.7, J1_20.6, J1_20.7, J1_21.6, J1_21.7, J1_22.6, J1_22.7, J1_23.6, J1_23.7, J1_24.6, J1_24.7, J1_25.6, J1_25.7, J1_26.6, J1_26.7, J1_27.6, J1_27.7, J1_28.6, J1_28.7, J1_29.6, J1_29.7, J1_30.6, J1_30.7, J1_31.6, J1_31.7, J1_32.6, J1_32.7; also elsewhere on the board
R32: J1_01.2, J1_01.3, J1_02.2, J1_02.3, J1_03.2, J1_03.3, J1_04.2, J1_04.3, J1_05.2, J1_05.3, J1_06.2, J1_06.3, J1_08.2, J1_08.3, J1_09.2, J1_09.3, J1_10.2, J1_10.3, J1_11.2, J1_11.3, J1_12.2, J1_12.3, J1_13.2, J1_13.3, J1_14.2, J1_14.3, J1_15.2, J1_15.3, J1_16.2, J1_16.3, J1_17.2, J1_17.3, J1_18.2, J1_18.3, J1_19.2, J1_19.3, J1_20.2, J1_20.3, J1_21.2, J1_21.3, J1_22.2, J1_22.3, J1_23.2, J1_23.3, J1_24.2, J1_24.3, J1_25.2, J1_25.3, J1_26.2, J1_26.3, J1_27.2, J1_27.3, J1_28.2, J1_28.3, J1_29.2, J1_29.3, J1_30.2, J1_30.3, J1_31.2, J1_31.3, J1_32.2, J1_32.3; also elsewhere on the board
